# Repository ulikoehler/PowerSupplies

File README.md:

# PowerSupplies
Power supply PCBs &amp; documentation

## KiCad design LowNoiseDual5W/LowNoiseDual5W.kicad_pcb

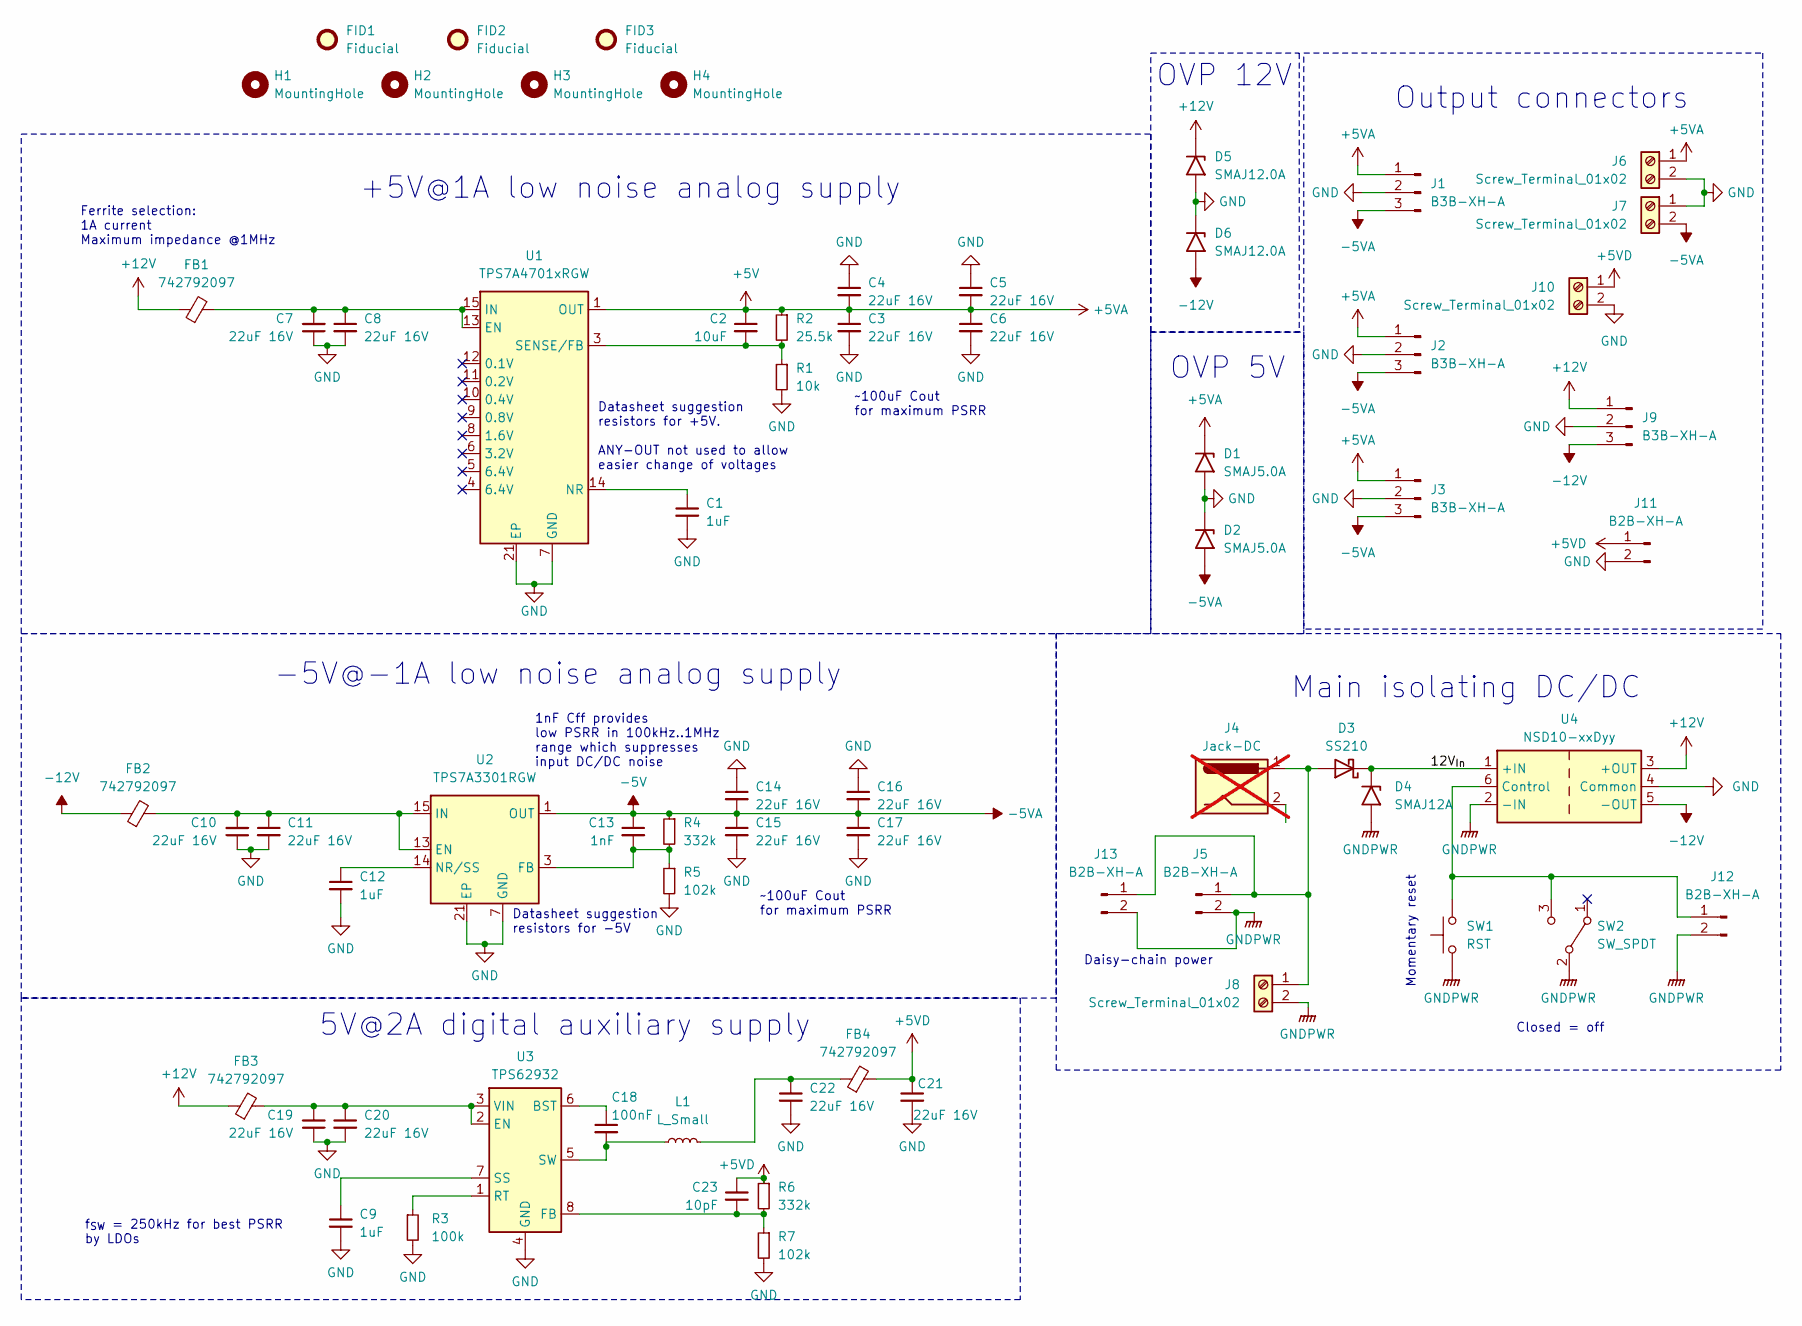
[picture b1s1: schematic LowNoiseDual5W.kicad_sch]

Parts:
C1, C9, C12: 1uF; R_0603_1608Metric
C2: 10uF; R_0603_1608Metric
C3, C4, C5, C6, C7, C8, C10, C11, C14, C15, C16, C17, C19, C20, C21, C22: 22uF 16V; C_1206_3216Metric; MPN CL31A226MOCLNNC
C13: 1nF; R_0603_1608Metric
C18: 100nF; R_0603_1608Metric
C23: 10pF; R_0603_1608Metric
D1, D2: SMAJ5.0A; D_SMA
D3: SS210; D_SMA
D4: SMAJ12A; D_SMA
D5, D6: SMAJ12.0A; D_SMA
FB1, FB2, FB3, FB4: 742792097; L_0805_2012Metric
FID1, FID2, FID3: Fiducial; Fiducial_0.5mm_Mask1mm
H1, H2, H3, H4: MountingHole; MountingHole_3.2mm_M3_ISO7380
J1, J2, J3, J9: B3B-XH-A; JST_XH_B3B-XH-A_1x03_P2.50mm_Vertical
J4: Jack-DC; BarrelJack_GCT_DCJ200-10-A_Horizontal; not fitted
J5, J11, J13: B2B-XH-A; JST_XH_B2B-XH-A_1x02_P2.50mm_Vertical
J6, J7, J8, J10: Screw_Terminal_01x02; TerminalBlock_Phoenix_MKDS-1,5-2-5.08_1x02_P5.08mm_Horizont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
J12: B2B-XH-A; JST_PH_B2B-PH-K_1x02_P2.00mm_Vertical
L1: L_Small; L_SXN_SMDRI127
R1: 10k; R_0603_1608Metric
R2: 25.5k; R_0603_1608Metric
R3: 100k; R_0603_1608Metric
R4, R6: 332k; R_0603_1608Metric
R5, R7: 102k; R_0603_1608Metric
SW1: RST; SW_SPST_TL3342; MPN TC-0522C-1.6-160G; LCSC Part # C2845287
SW2: SW_SPDT; SW_DPDT_CK_JS202011JCQN
U1: TPS7A4701xRGW; Texas_S-PVQFN-N20_EP3.15x3.15mm
U2: TPS7A3301RGW; Texas_S-PVQFN-N20_EP3.15x3.15mm
U3: TPS62932; SOT-583-8
U4: NSD10-xxDyy; Converter_DCDC_MeanWell_NSD10_THT

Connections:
+5V: C2.1, C3.1, C4.2, C5.2, C6.1, D1.1 (A1), J1.1, J2.1, J3.1, J6.1, R2.1, U1.1 (OUT), U1.20 (OUT)
+5VD: C21.1, C23.1, FB4.2, J10.1, J11.1, R6.1
+12V: D5.1 (A1), FB1.1, FB3.1, J9.1, U4.3 (+OUT)
-5V: C13.1, C14.2, C15.1, C16.2, C17.1, D2.2 (A2), J1.3, J2.3, J3.3, J7.2, R4.1, U2.1 (OUT), U2.20 (OUT)
-12V: D6.2 (A2), FB2.1, J9.3, U4.5 (-OUT)
/12V_{In}: D3.1 (K), D4.1 (A1), U4.1 (+IN)
GND: C1.2, C3.2, C4.1, C5.1, C6.2, C7.1, C8.2, C9.2, C10.1, C11.2, C12.2, C14.1, C15.2, C16.1, C17.2, C19.1, C20.2, C21.2, C22.2, D1.2 (A2), D2.1 (A1), D5.2 (A2), D6.1 (A1), J1.2, J2.2, J3.2, J6.2, J7.1, J9.2, J10.2, J11.2, R1.2, R3.2, R5.2, R7.2, U1.7 (GND), U1.21 (EP), U2.7 (GND), U2.21 (EP), U3.4 (GND), U4.4 (Common)
GNDPWR: D4.2 (A2), J5.2, J8.2, J12.2, J13.2, SW1.2, SW2.2 (B), U4.2 (-IN)
IN: C10.2, C11.1, FB2.2, U2.13 (EN), U2.15 (IN), U2.16 (IN)
unnamed: C22.1, FB4.1, L1.2
unnamed: D3.2 (A), J4.1, J5.1, J8.1, J13.1
unnamed: J12.1, SW1.1, SW2.3 (C), U4.6 (Control)
unnamed: C7.2, C8.1, FB1.2, U1.13 (EN), U1.15 (IN), U1.16 (IN)
unnamed: C1.1, U1.14 (NR)
unnamed: C2.2, R1.1, R2.2, U1.3 (SENSE/FB)
unnamed: C13.2, R4.2, R5.1, U2.3 (FB)
unnamed: C12.1, U2.14 (NR/SS)
unnamed: C18.1, U3.6 (BST)
unnamed: C19.2, C20.1, FB3.2, U3.2 (EN), U3.3 (VIN)
unnamed: C23.2, R6.2, R7.1, U3.8 (FB)
unnamed: R3.1, U3.1 (RT)
unnamed: C9.1, U3.7 (SS)
unnamed: C18.2, L1.1, U3.5 (SW)

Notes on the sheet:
OVP 12V
-5V@-1A low noise analog supply
f_{SW} = 250kHz for best PSRR by LDOs
~100uF Cout for maximum PSRR
Closed = off
1nF Cff provides low PSRR in 100kHz..1MHz range which suppresses input DC/DC noise
+5V@1A low noise analog supply
Momentary reset
Main isolating DC/DC
Datasheet suggestion resistors for +5V. ANY-OUT not used to allow easier change of voltages
Ferrite selection: 1A current Maximum impedance @1MHz
Daisy-chain power
OVP 5V
5V@2A digital auxiliary supply
Datasheet suggestion resistors for -5V
Output connectors

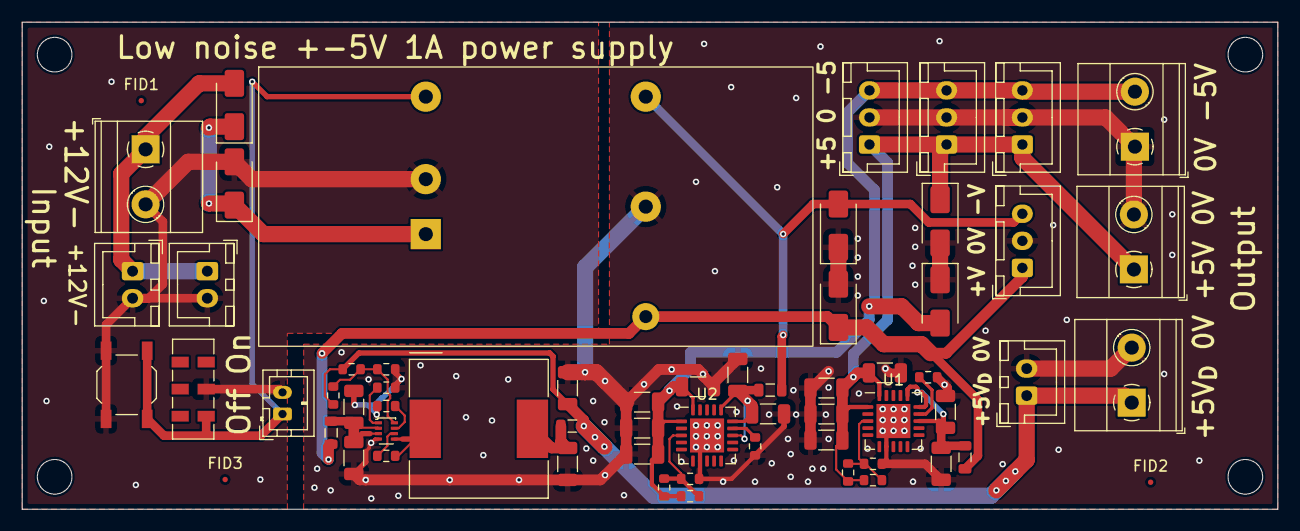
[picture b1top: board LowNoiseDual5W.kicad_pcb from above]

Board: 2 copper layers, 116.0 x 45.0 mm, 66 parts (0 on the bottom side), 23 nets.

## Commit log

2024-01-04 Initialize low noise dual 5W project
2024-01-07 Implement low noise dual 5W power supply
2024-01-07 Add fiducials
